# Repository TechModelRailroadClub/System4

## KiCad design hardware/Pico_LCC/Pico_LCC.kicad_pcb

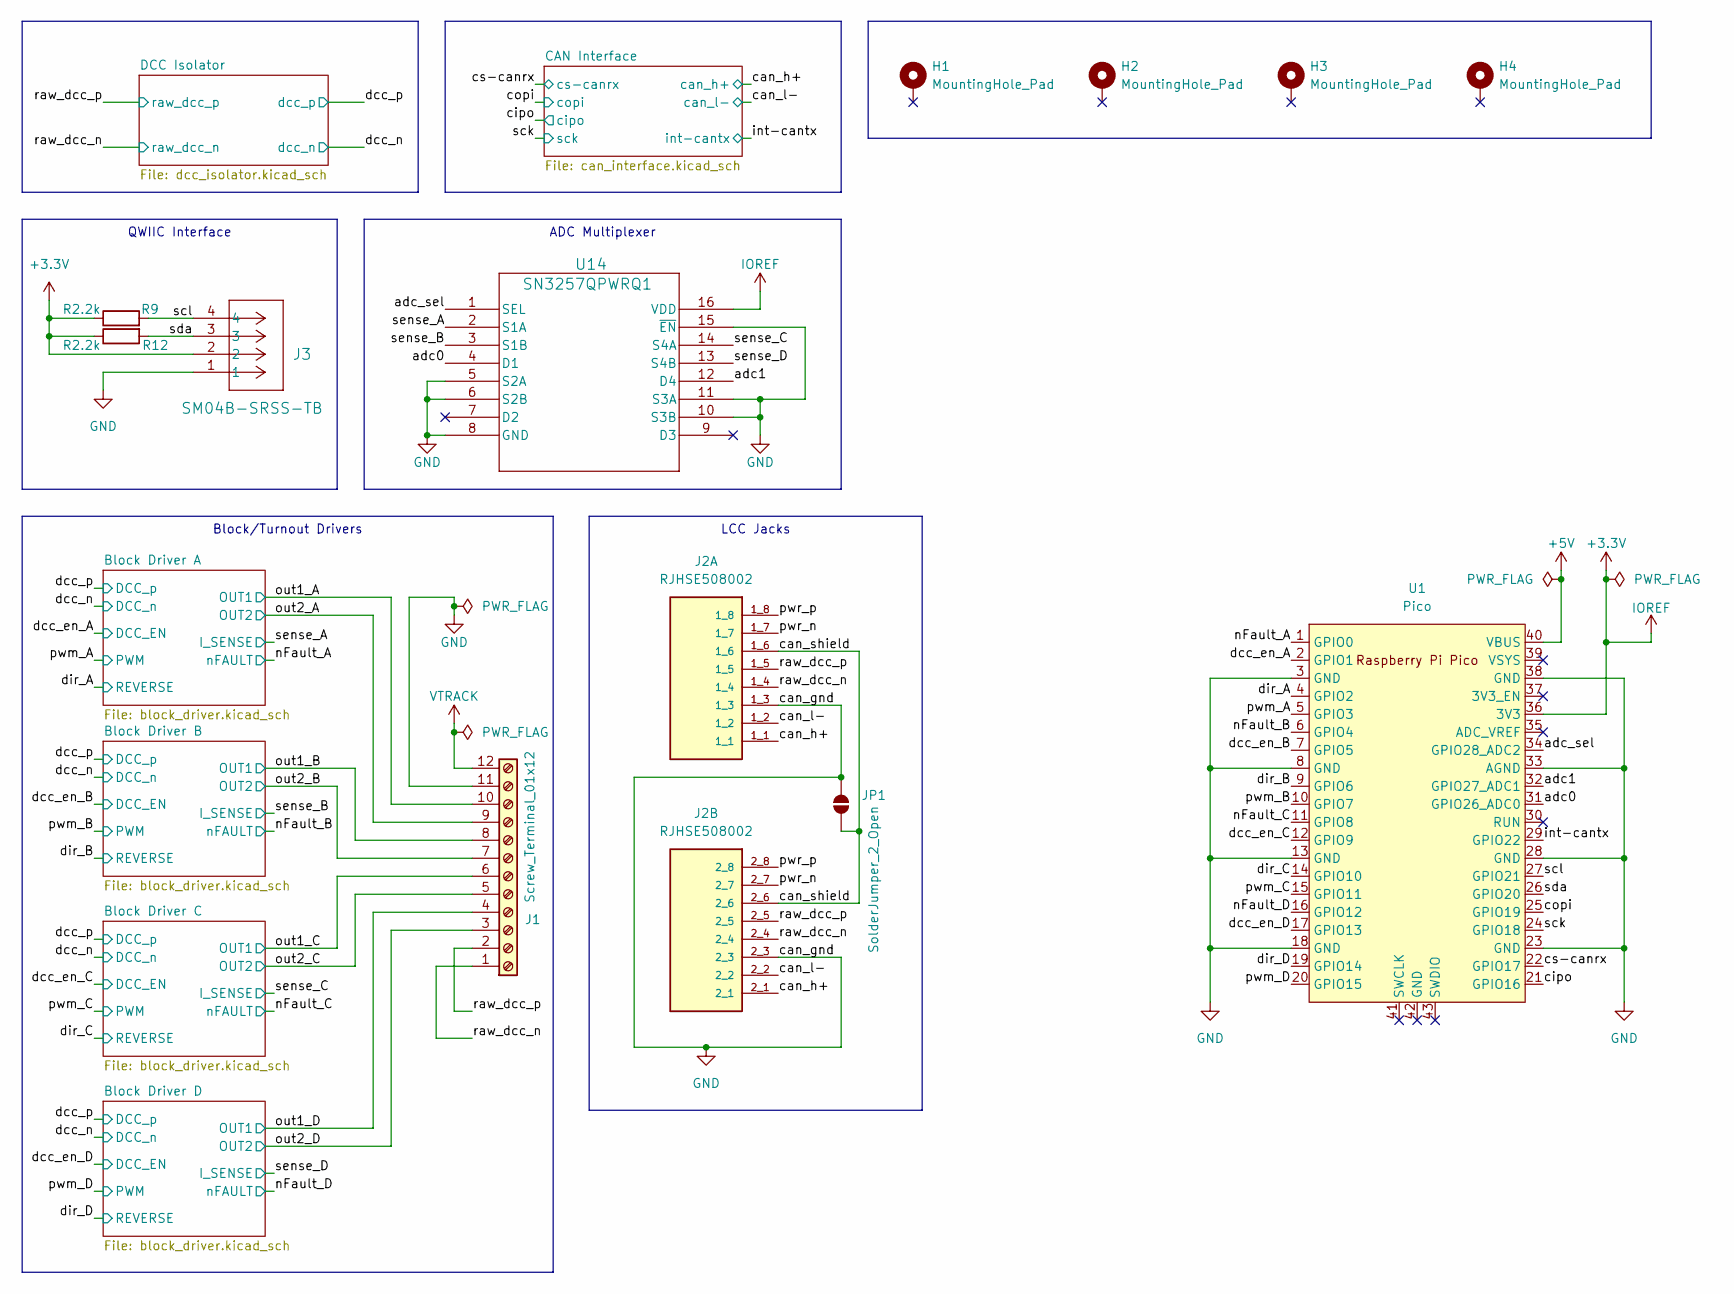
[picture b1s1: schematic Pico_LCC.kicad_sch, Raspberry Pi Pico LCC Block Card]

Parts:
H1, H2, H3, H4: MountingHole_Pad; MountingHole_4.3mm_M4_Pad_Via
J1: Screw_Terminal_01x12; TerminalBlock_Phoenix_MKDS-1,5-12_1x12_P5.00mm_Horizontal; Manufacturer Part Number 1753611
J2: RJHSE508002; AMPHENOL_RJHSE508002; PARTREV E
J3: SM04B-SRSS-TB; CONN_SM04B-SRSS-TB_JST
JP1: SolderJumper_2_Open; SolderJumper-2_P1.3mm_Open_RoundedPad1.0x1.5mm
R9, R12: R2.2k; R_0805_2012Metric_Pad1.20x1.40mm_HandSolder; Manufacturer Part Number ERJ6ENF4702V
U1: Pico; RPi_Pico_SMD_TH
U14: SN3257QPWRQ1; SOIC_PRQ1_TEX

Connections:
+3.3V: J3.2, R9.1, R12.1, U1.36 (3V3), U14.16 (VDD); also elsewhere on the board
+5V: U1.40 (VBUS); also elsewhere on the board
/adc0: U1.31 (GPIO26_ADC0), U14.4 (D1)
/adc1: U1.32 (GPIO27_ADC1), U14.12 (D4)
/adc_sel: U1.34 (GPIO28_ADC2), U14.1 (SEL)
/can_h+: J2.1_1, J2.2_1; also elsewhere on the board
/can_l-: J2.1_2, J2.2_2; also elsewhere on the board
/can_shield: J2.1_6, J2.2_6, JP1.1 (A)
/cipo: U1.21 (GPIO16); also elsewhere on the board
/copi: U1.25 (GPIO19); also elsewhere on the board
/cs-canrx: U1.22 (GPIO17); also elsewhere on the board
/dcc_en_A: U1.2 (GPIO1); also elsewhere on the board
/dcc_en_B: U1.7 (GPIO5); also elsewhere on the board
/dcc_en_C: U1.12 (GPIO9); also elsewhere on the board
/dcc_en_D: U1.17 (GPIO13); also elsewhere on the board
/dir_A: U1.4 (GPIO2); also elsewhere on the board
/dir_B: U1.9 (GPIO6); also elsewhere on the board
/dir_C: U1.14 (GPIO10); also elsewhere on the board
/dir_D: U1.19 (GPIO14); also elsewhere on the board
/int-cantx: U1.29 (GPIO22); also elsewhere on the board
/nFault_A: U1.1 (GPIO0); also elsewhere on the board
/nFault_B: U1.6 (GPIO4); also elsewhere on the board
/nFault_C: U1.11 (GPIO8); also elsewhere on the board
/nFault_D: U1.16 (GPIO12); also elsewhere on the board
/out1_A: J1.10; also elsewhere on the board
/out1_B: J1.8; also elsewhere on the board
/out1_C: J1.6; also elsewhere on the board
/out1_D: J1.4; also elsewhere on the board
/out2_A: J1.9; also elsewhere on the board
/out2_B: J1.7; also elsewhere on the board
/out2_C: J1.5; also elsewhere on the board
/out2_D: J1.3; also elsewhere on the board
/pwm_A: U1.5 (GPIO3); also elsewhere on the board
/pwm_B: U1.10 (GPIO7); also elsewhere on the board
/pwm_C: U1.15 (GPIO11); also elsewhere on the board
/pwm_D: U1.20 (GPIO15); also elsewhere on the board
/pwr_n: J2.1_7, J2.2_7
/pwr_p: J2.1_8, J2.2_8
/raw_dcc_n: J1.1, J2.1_4, J2.2_4; also elsewhere on the board
/raw_dcc_p: J1.2, J2.1_5, J2.2_5; also elsewhere on the board
/sck: U1.24 (GPIO18); also elsewhere on the board
/scl: J3.4, R9.2, U1.27 (GPIO21)
/sda: J3.3, R12.2, U1.26 (GPIO20)
/sense_A: U14.2 (S1A); also elsewhere on the board
/sense_B: U14.3 (S1B); also elsewhere on the board
/sense_C: U14.14 (S4A); also elsewhere on the board
/sense_D: U14.13 (S4B); also elsewhere on the board
GND: J1.11, J2.1_3, J2.2_3, J3.1, JP1.2 (B), U1.3 (GND), U1.8 (GND), U1.13 (GND), U1.18 (GND), U1.23 (GND), U1.28 (GND), U1.33 (AGND), U1.38 (GND), U14.5 (S2A), U14.6 (S2B), U14.8 (GND), U14.10 (S3B), U14.11 (S3A), U14.15 (~EN); also elsewhere on the board
VTRACK: J1.12; also elsewhere on the board

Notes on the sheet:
Block/Turnout Drivers
QWIIC Interface
LCC Jacks
ADC Multiplexer

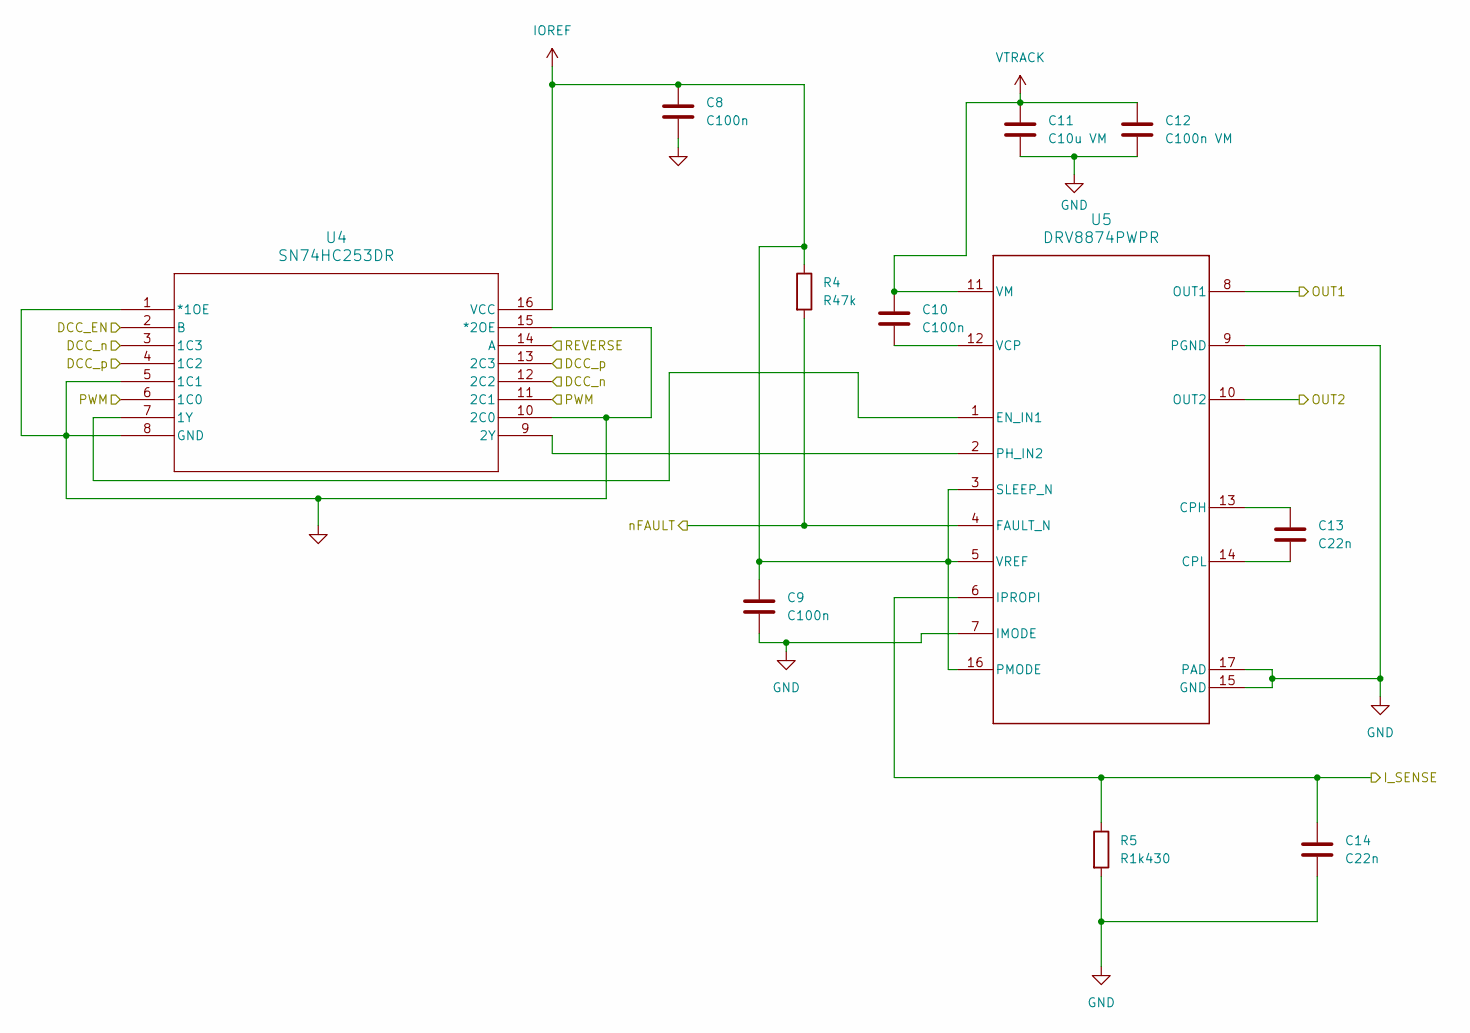
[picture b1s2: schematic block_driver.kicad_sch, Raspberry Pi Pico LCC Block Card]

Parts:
C8, C9, C10: C100n; C_0805_2012Metric_Pad1.18x1.45mm_HandSolder; Manufacturer Part Number CL21B104KACNFNC
C11: C10u VM; C_1206_3216Metric_Pad1.33x1.80mm_HandSolder; Manufacturer Part Number CL31A106KBHNNNE
C12: C100n VM; C_0805_2012Metric_Pad1.18x1.45mm_HandSolder; Manufacturer Part Number CL21B104KBFXPJE
C13, C14: C22n; C_0805_2012Metric_Pad1.18x1.45mm_HandSolder; Manufacturer Part Number CL21B223JBANNNC
R4: R47k; R_0805_2012Metric_Pad1.20x1.40mm_HandSolder; Manufacturer Part Number ERJ6ENF4702V
R5: R1k430; R_0805_2012Metric_Pad1.20x1.40mm_HandSolder; Manufacturer Part Number RC0805FR-071K43L
U4: SN74HC253DR; SO-16_3.9x9.9mm_P1.27mm; Manufacturer Part Number SN74HC253DR
U5: DRV8874PWPR; PWP0016J_NV; Manufacturer Part Number DRV8874PWPR

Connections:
+3.3V: C8.1, C9.1, R4.1, U4.16 (VCC), U5.3 (SLEEP_N), U5.5 (VREF), U5.16 (PMODE); also elsewhere on the board
/dcc_en_B: U4.2 (B); also elsewhere on the board
/dcc_n: U4.3 (1C3), U4.12 (2C2); also elsewhere on the board
/dcc_p: U4.4 (1C2), U4.13 (2C3); also elsewhere on the board
/dir_B: U4.14 (A); also elsewhere on the board
/nFault_B: R4.2, U5.4 (FAULT_N); also elsewhere on the board
/out1_B: U5.8 (OUT1); also elsewhere on the board
/out2_B: U5.10 (OUT2); also elsewhere on the board
/pwm_B: U4.6 (1C0), U4.11 (2C1); also elsewhere on the board
/sense_B: C14.1, R5.1, U5.6 (IPROPI); also elsewhere on the board
GND: C8.2, C9.2, C11.2, C12.2, C14.2, R5.2, U4.1 (*1OE), U4.5 (1C1), U4.8 (GND), U4.10 (2C0), U4.15 (*2OE), U5.7 (IMODE), U5.9 (PGND), U5.15 (GND), U5.17 (PAD); also elsewhere on the board
unnamed: U4.7 (1Y), U5.1 (EN_IN1)
unnamed: U4.9 (2Y), U5.2 (PH_IN2)
unnamed: C13.1, U5.13 (CPH)
unnamed: C13.2, U5.14 (CPL)
unnamed: C10.2, U5.12 (VCP)
VTRACK: C10.1, C11.1, C12.1, U5.11 (VM); also elsewhere on the board

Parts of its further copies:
C1, C2, C3, C15, C16, C17, C22, C23, C24: C100n; C_0805_2012Metric_Pad1.18x1.45mm_HandSolder; Manufacturer Part Number CL21B104KACNFNC
C4, C18, C25: C10u VM; C_1206_3216Metric_Pad1.33x1.80mm_HandSolder; Manufacturer Part Number CL31A106KBHNNNE
C5, C19, C26: C100n VM; C_0805_2012Metric_Pad1.18x1.45mm_HandSolder; Manufacturer Part Number CL21B104KBFXPJE
C6, C7, C20, C21, C27, C28: C22n; C_0805_2012Metric_Pad1.18x1.45mm_HandSolder; Manufacturer Part Number CL21B223JBANNNC
R1, R7, R10: R47k; R_0805_2012Metric_Pad1.20x1.40mm_HandSolder; Manufacturer Part Number ERJ6ENF4702V
R2, R8, R11: R1k430; R_0805_2012Metric_Pad1.20x1.40mm_HandSolder; Manufacturer Part Number RC0805FR-071K43L
U2, U6, U8: SN74HC253DR; SO-16_3.9x9.9mm_P1.27mm; Manufacturer Part Number SN74HC253DR
U3, U7, U9: DRV8874PWPR; PWP0016J_NV; Manufacturer Part Number DRV8874PWPR

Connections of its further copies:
+3.3V: C1.1, C2.1, C15.1, C16.1, C22.1, C23.1, R1.1, R7.1, R10.1, U2.16 (VCC), U3.3 (SLEEP_N), U3.5 (VREF), U3.16 (PMODE), U6.16 (VCC), U7.3 (SLEEP_N), U7.5 (VREF), U7.16 (PMODE), U8.16 (VCC), U9.3 (SLEEP_N), U9.5 (VREF), U9.16 (PMODE); also elsewhere on the board
/dcc_en_A: U2.2 (B); also elsewhere on the board
/dcc_en_C: U6.2 (B); also elsewhere on the board
/dcc_en_D: U8.2 (B); also elsewhere on the board
/dcc_n: U2.3 (1C3), U2.12 (2C2), U6.3 (1C3), U6.12 (2C2), U8.3 (1C3), U8.12 (2C2); also elsewhere on the board
/dcc_p: U2.4 (1C2), U2.13 (2C3), U6.4 (1C2), U6.13 (2C3), U8.4 (1C2), U8.13 (2C3); also elsewhere on the board
/dir_A: U2.14 (A); also elsewhere on the board
/dir_C: U6.14 (A); also elsewhere on the board
/dir_D: U8.14 (A); also elsewhere on the board
/nFault_A: R1.2, U3.4 (FAULT_N); also elsewhere on the board
/nFault_C: R7.2, U7.4 (FAULT_N); also elsewhere on the board
/nFault_D: R10.2, U9.4 (FAULT_N); also elsewhere on the board
/out1_A: U3.8 (OUT1); also elsewhere on the board
/out1_C: U7.8 (OUT1); also elsewhere on the board
/out1_D: U9.8 (OUT1); also elsewhere on the board
/out2_A: U3.10 (OUT2); also elsewhere on the board
/out2_C: U7.10 (OUT2); also elsewhere on the board
/out2_D: U9.10 (OUT2); also elsewhere on the board
/pwm_A: U2.6 (1C0), U2.11 (2C1); also elsewhere on the board
/pwm_C: U6.6 (1C0), U6.11 (2C1); also elsewhere on the board
/pwm_D: U8.6 (1C0), U8.11 (2C1); also elsewhere on the board
/sense_A: C7.1, R2.1, U3.6 (IPROPI); also elsewhere on the board
/sense_C: C21.1, R8.1, U7.6 (IPROPI); also elsewhere on the board
/sense_D: C28.1, R11.1, U9.6 (IPROPI); also elsewhere on the board
GND: C1.2, C2.2, C4.2, C5.2, C7.2, C15.2, C16.2, C18.2, C19.2, C21.2, C22.2, C23.2, C25.2, C26.2, C28.2, R2.2, R8.2, R11.2, U2.1 (*1OE), U2.5 (1C1), U2.8 (GND), U2.10 (2C0), U2.15 (*2OE), U3.7 (IMODE), U3.9 (PGND), U3.15 (GND), U3.17 (PAD), U6.1 (*1OE), U6.5 (1C1), U6.8 (GND), U6.10 (2C0), U6.15 (*2OE), U7.7 (IMODE), U7.9 (PGND), U7.15 (GND), U7.17 (PAD), U8.1 (*1OE), U8.5 (1C1), U8.8 (GND), U8.10 (2C0), U8.15 (*2OE), U9.7 (IMODE), U9.9 (PGND), U9.15 (GND), U9.17 (PAD); also elsewhere on the board
unnamed: U2.7 (1Y), U3.1 (EN_IN1)
unnamed: U2.9 (2Y), U3.2 (PH_IN2)
unnamed: C6.1, U3.13 (CPH)
unnamed: C6.2, U3.14 (CPL)
unnamed: C3.2, U3.12 (VCP)
unnamed: U6.7 (1Y), U7.1 (EN_IN1)
unnamed: U6.9 (2Y), U7.2 (PH_IN2)
unnamed: C20.1, U7.13 (CPH)
unnamed: C20.2, U7.14 (CPL)
unnamed: C17.2, U7.12 (VCP)
unnamed: U8.7 (1Y), U9.1 (EN_IN1)
unnamed: U8.9 (2Y), U9.2 (PH_IN2)
unnamed: C27.1, U9.13 (CPH)
unnamed: C27.2, U9.14 (CPL)
unnamed: C24.2, U9.12 (VCP)
VTRACK: C3.1, C4.1, C5.1, C17.1, C18.1, C19.1, C24.1, C25.1, C26.1, U3.11 (VM), U7.11 (VM), U9.11 (VM); also elsewhere on the board

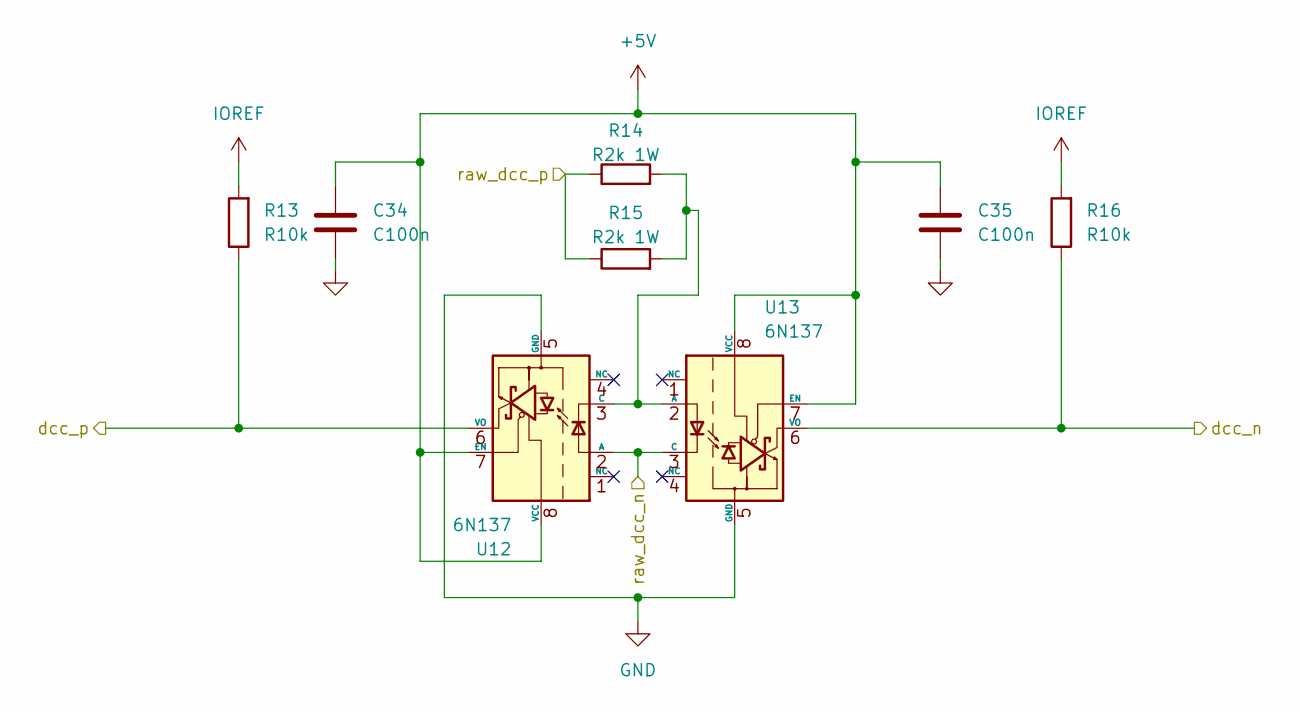
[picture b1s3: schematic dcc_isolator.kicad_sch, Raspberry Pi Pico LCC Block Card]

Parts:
C34, C35: C100n; C_0805_2012Metric_Pad1.18x1.45mm_HandSolder; Manufacturer Part Number CL21B104KACNFNC
R13, R16: R10k; R_0805_2012Metric_Pad1.20x1.40mm_HandSolder; Manufacturer Part Number RC0805JR-0710KL
R14, R15: R2k 1W; R_2512_6332Metric_Pad1.40x3.35mm_HandSolder; Manufacturer Part Number AC2512JK-072KL
U12, U13: 6N137; DIP-8_W7.62mm_SMDSocket_SmallPads; Manufacturer Part Number 6N137S-TA1-L

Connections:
+3.3V: R13.2, R16.2; also elsewhere on the board
+5V: C34.1, C35.1, U12.7 (EN), U12.8 (VCC), U13.7 (EN), U13.8 (VCC); also elsewhere on the board
/dcc_n: R16.1, U13.6 (VO); also elsewhere on the board
/dcc_p: R13.1, U12.6 (VO); also elsewhere on the board
/raw_dcc_n: U12.2 (A), U13.3 (C); also elsewhere on the board
/raw_dcc_p: R14.1, R15.1; also elsewhere on the board
GND: C34.2, C35.2, U12.5 (GND), U13.5 (GND); also elsewhere on the board
unnamed: R14.2, R15.2, U12.3 (C), U13.2 (A)

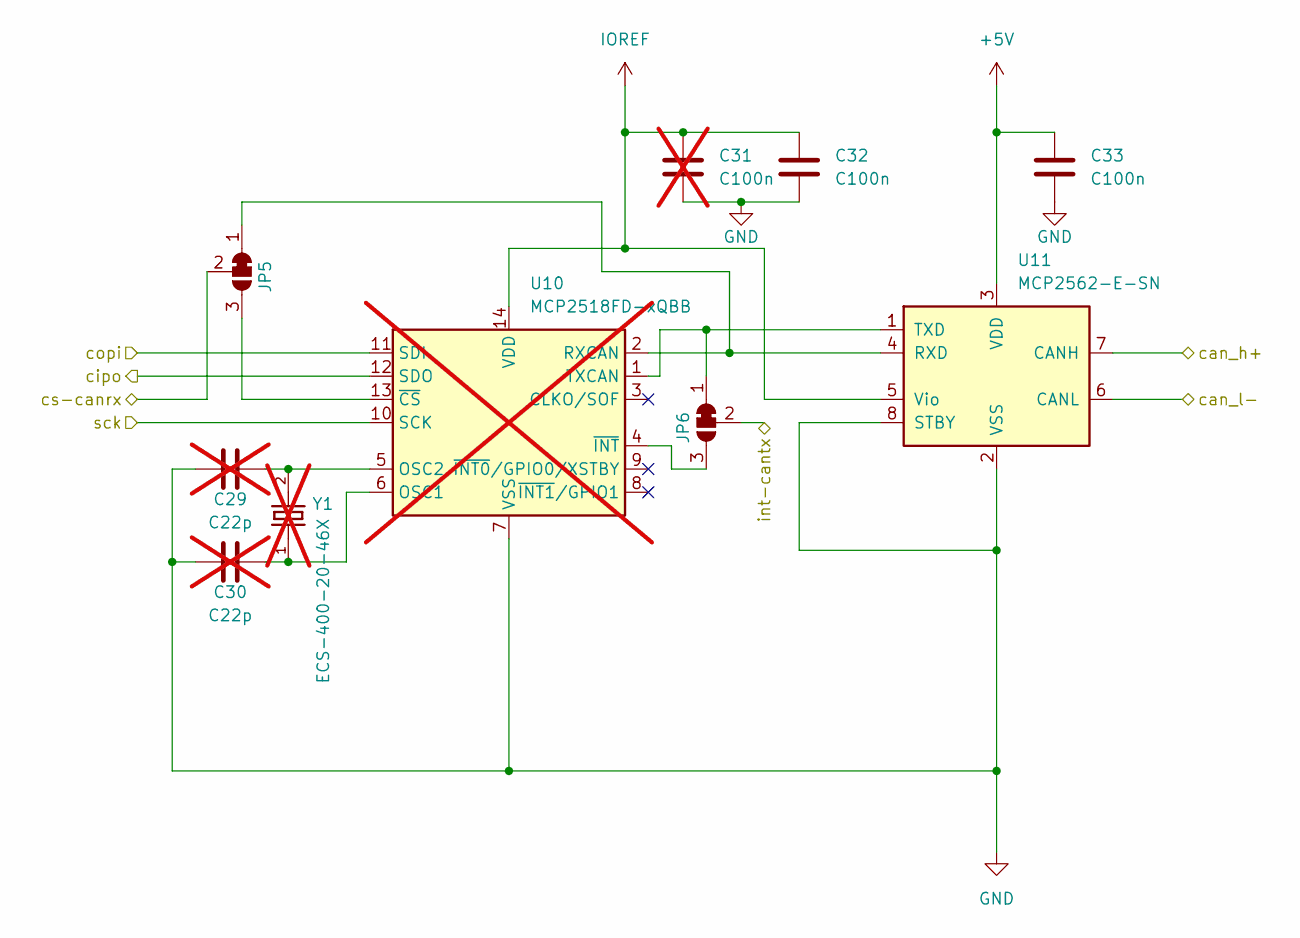
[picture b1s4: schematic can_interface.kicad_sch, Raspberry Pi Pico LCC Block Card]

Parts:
C29, C30: C22p; C_0805_2012Metric_Pad1.18x1.45mm_HandSolder; not fitted
C31: C100n; C_0805_2012Metric_Pad1.18x1.45mm_HandSolder; not fitted
C32, C33: C100n; C_0805_2012Metric_Pad1.18x1.45mm_HandSolder; Manufacturer Part Number CL21B104KACNFNC
JP5, JP6: SolderJumper_3_Bridged12; SolderJumper-3_P1.3mm_Bridged12_RoundedPad1.0x1.5mm_NumberL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
U10: MCP2518FD-xQBB; SOIC-14_3.9x8.7mm_P1.27mm; not fitted
U11: MCP2562-E-SN; SOIC-8_3.9x4.9mm_P1.27mm; Manufacturer Part Number MCP2562-E-SN
Y1: ECS-400-20-46X; XTAL_ECS-400-20-46X; not fitted

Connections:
+3.3V: C31.1, C32.1, U10.14 (VDD), U11.5 (Vio); also elsewhere on the board
+5V: C33.1, U11.3 (VDD); also elsewhere on the board
/can_h+: U11.7 (CANH); also elsewhere on the board
/can_l-: U11.6 (CANL); also elsewhere on the board
/cipo: U10.12 (SDO); also elsewhere on the board
/copi: U10.11 (SDI); also elsewhere on the board
/cs-canrx: JP5.2 (C); also elsewhere on the board
/int-cantx: JP6.2 (C); also elsewhere on the board
/sck: U10.10 (SCK); also elsewhere on the board
GND: C29.1, C30.1, C31.2, C32.2, C33.2, U10.7 (VSS), U10.15 (VSS), U11.2 (VSS), U11.8 (STBY); also elsewhere on the board
unnamed: JP5.1 (A), U10.2 (RXCAN), U11.4 (RXD)
unnamed: JP5.3 (B), U10.13 (~CS)
unnamed: JP6.1 (A), U10.1 (TXCAN), U11.1 (TXD)
unnamed: JP6.3 (B), U10.4 (~INT)
unnamed: C30.2, U10.6 (OSC1), Y1.1
unnamed: C29.2, U10.5 (OSC2), Y1.2

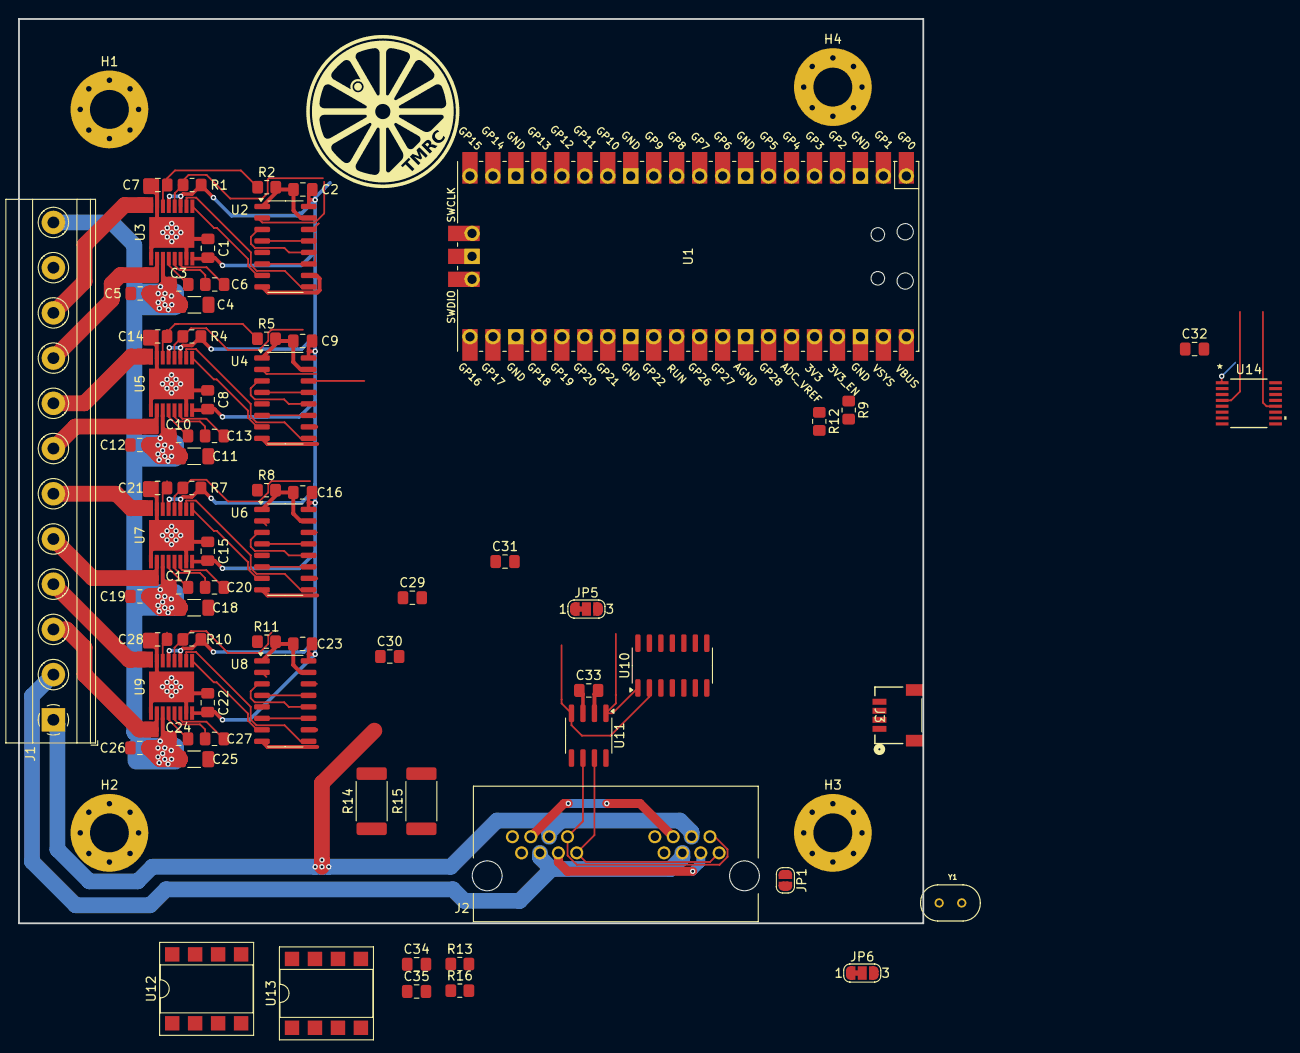
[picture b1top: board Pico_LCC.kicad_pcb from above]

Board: 2 copper layers, 100.0 x 100.0 mm, 74 parts (0 on the bottom side), 78 nets.

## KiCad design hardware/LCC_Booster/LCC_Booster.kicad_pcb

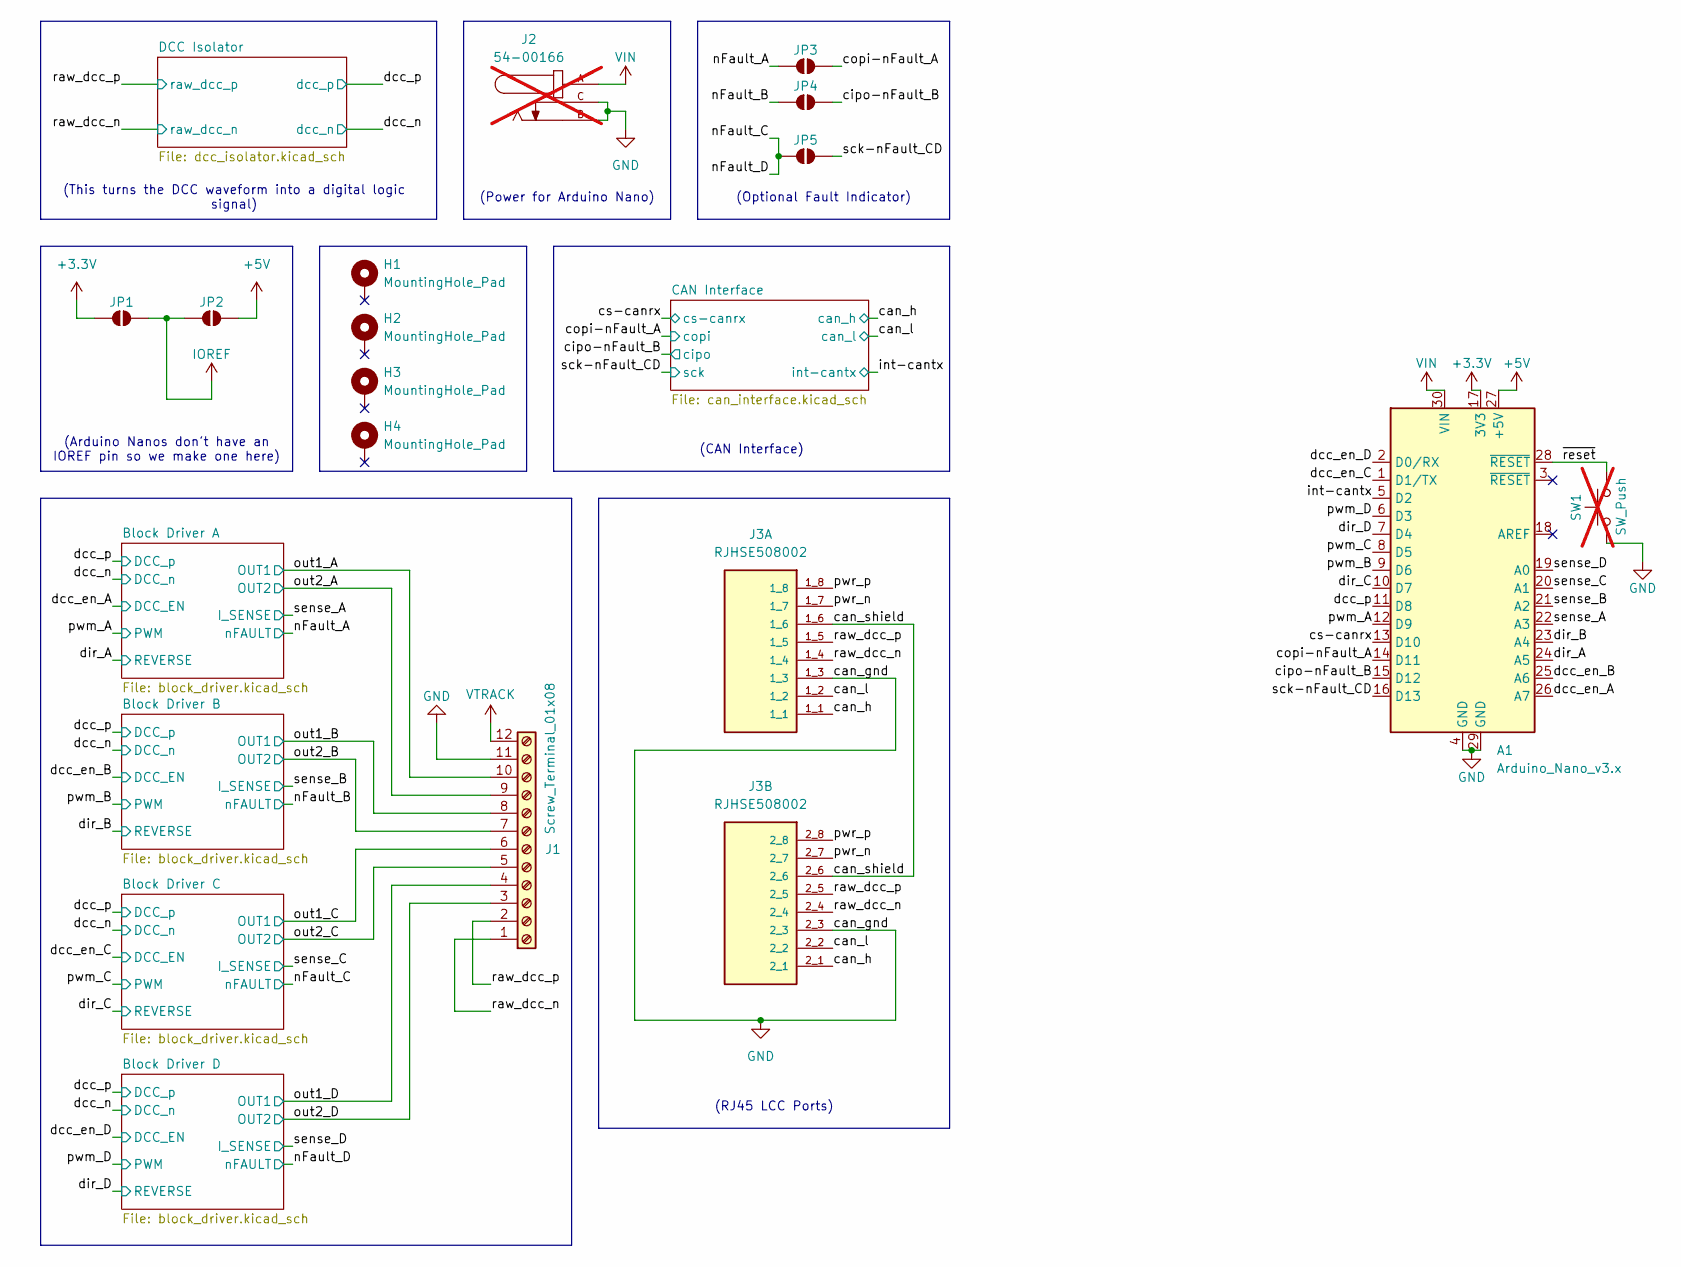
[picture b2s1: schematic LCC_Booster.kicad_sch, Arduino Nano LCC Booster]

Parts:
A1: Arduino_Nano_v3.x; Arduino_Nano; Manufacturer Part Number L432KC
H1, H2, H3, H4: MountingHole_Pad; MountingHole_4.3mm_M4_Pad_Via
J1: Screw_Terminal_01x08; TerminalBlock_Phoenix_MKDS-1,5-12_1x12_P5.00mm_Horizontal; Manufacturer Part Number 1753611
J2: 54-00166; TENSILITY_54-00166; PARTREV A; not fitted
J3: RJHSE508002; AMPHENOL_RJHSE508002; PARTREV E
JP1, JP2, JP3, JP4, JP5: SolderJumper_2_Open; SolderJumper-2_P1.3mm_Open_RoundedPad1.0x1.5mm
SW1: SW_Push; SW_PUSH_6mm_H4.3mm; not fitted

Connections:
+3.3V: A1.17 (3V3), JP1.1 (A)
+5V: A1.27 (+5V), JP2.2 (B); also elsewhere on the board
/can_h: J3.1_1, J3.2_1; also elsewhere on the board
/can_l: J3.1_2, J3.2_2; also elsewhere on the board
/can_shield: J3.1_6, J3.2_6
/cipo-nFault_B: A1.15 (D12), JP4.2 (B); also elsewhere on the board
/copi-nFault_A: A1.14 (D11), JP3.2 (B); also elsewhere on the board
/cs-canrx: A1.13 (D10); also elsewhere on the board
/dcc_en_A: A1.26 (A7); also elsewhere on the board
/dcc_en_B: A1.25 (A6); also elsewhere on the board
/dcc_en_C: A1.1 (D1/TX); also elsewhere on the board
/dcc_en_D: A1.2 (D0/RX); also elsewhere on the board
/dcc_p: A1.11 (D8); also elsewhere on the board
/dir_A: A1.24 (A5); also elsewhere on the board
/dir_B: A1.23 (A4); also elsewhere on the board
/dir_C: A1.10 (D7); also elsewhere on the board
/dir_D: A1.7 (D4); also elsewhere on the board
/int-cantx: A1.5 (D2); also elsewhere on the board
/nFault_A: JP3.1 (A); also elsewhere on the board
/nFault_B: JP4.1 (A); also elsewhere on the board
/nFault_C: JP5.1 (A); also elsewhere on the board
/out1_A: J1.10; also elsewhere on the board
/out1_B: J1.8; also elsewhere on the board
/out1_C: J1.6; also elsewhere on the board
/out1_D: J1.4; also elsewhere on the board
/out2_A: J1.9; also elsewhere on the board
/out2_B: J1.7; also elsewhere on the board
/out2_C: J1.5; also elsewhere on the board
/out2_D: J1.3; also elsewhere on the board
/pwm_A: A1.12 (D9); also elsewhere on the board
/pwm_B: A1.9 (D6); also elsewhere on the board
/pwm_C: A1.8 (D5); also elsewhere on the board
/pwm_D: A1.6 (D3); also elsewhere on the board
/pwr_n: J3.1_7, J3.2_7
/pwr_p: J3.1_8, J3.2_8
/raw_dcc_n: J1.1, J3.1_4, J3.2_4; also elsewhere on the board
/raw_dcc_p: J1.2, J3.1_5, J3.2_5; also elsewhere on the board
/sck-nFault_CD: A1.16 (D13), JP5.2 (B); also elsewhere on the board
/sense_A: A1.22 (A3); also elsewhere on the board
/sense_B: A1.21 (A2); also elsewhere on the board
/sense_C: A1.20 (A1); also elsewhere on the board
/sense_D: A1.19 (A0); also elsewhere on the board
/~reset: A1.28 (~RESET), SW1.2
GND: A1.4 (GND), A1.29 (GND), J1.11, J2.B, J2.C, J3.1_3, J3.2_3, SW1.1; also elsewhere on the board
IOREF: JP1.2 (B), JP2.1 (A); also elsewhere on the board
VIN: A1.30 (VIN), J2.A
VTRACK: J1.12; also elsewhere on the board

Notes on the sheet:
(Arduino Nanos don't have an IOREF pin so we make one here)
(RJ45 LCC Ports)
(Power for Arduino Nano)
(This turns the DCC waveform into a digital logic signal)
(CAN Interface)
(Optional Fault Indicator)
